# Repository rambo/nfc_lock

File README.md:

nfc_lock
========

(more) secure electric lock with DESFire EV1 NFC tags

## libnfc and libfreefare

    sudo apt-add-repository ppa:christopher-hoskin/ppa
    sudo apt-get update
    sudo apt-get install libnfc5 libnfc-bin libnfc-pn53x-examples libnfc-examples
    sudo apt-get install libfreefare0 libfreefare-bin
    sudo apt-get install python-zmq python-yaml python-tornado

`python-yaml` and `python-tornado` can be installed to virtualenv (esp tornado might be better to install via pip even if not to virtualenv the deb pulls unneccessary dependencies), zmq will be painful to install via pip, use the system package.

### For compiling

For the C programs.

    sudo apt-get install libfreefare-dev libnfc-dev libssl-dev pkg-config libzmq-dev

### RasPi

All libraries should be part of normal releases now.

## Terms

  - Card (PICC in NXP terms): The DESFire EV1 chip+antenna in a package (fob, card, sticker...)
  - Pre-Personalization step: Where card default master key is changed and applications are defined.
  - Application: collection of files on the card, application can have multiple keys for various purposes
  - Provisioning (or personalization) step: Where a personalized card is issued to a card holder and the card (plus backing datababase) is updated with relevant info
  - Diversified key: Key that has been derived from a master key via the method described in NXP AN19022

## SQLite for keys

Create a test file `sqlite3 keys.db`:

    CREATE TABLE valid_tokens (value TEXT UNIQUE, type INTEGER, acl INTEGER, external_ids TEXT);
    CREATE TABLE revoked_tokens (value TEXT UNIQUE, type INTEGER);

Prepare some tags and insert their (real) UIDs to the grants and revokes

    INSERT INTO revoked_tokens VALUES ("04453069b21e80");
    INSERT INTO valid_tokens VALUES ("04212f69b21e80", 0, 1);

In reality you will generate this file based on your person registry (keep track of validity times etc there, then regenerate the keydb for the door).

## Hacking

Remember to valgrind your C programs (`valgrind -v --leak-check=yes  myprog args`) at the same time as you do general functionality testing.

### RasPi

It seems Valgrind does not (and will not) support some instructions we use to talk with the NFC chips, see (this stackoverflow)[valgrindworkaround] for a workaround.

[valgrindworkaround]: http://stackoverflow.com/questions/20066215/valgrind-unrecognizes-memcmp-instruction-in-raspberry-pi#comment-29892760

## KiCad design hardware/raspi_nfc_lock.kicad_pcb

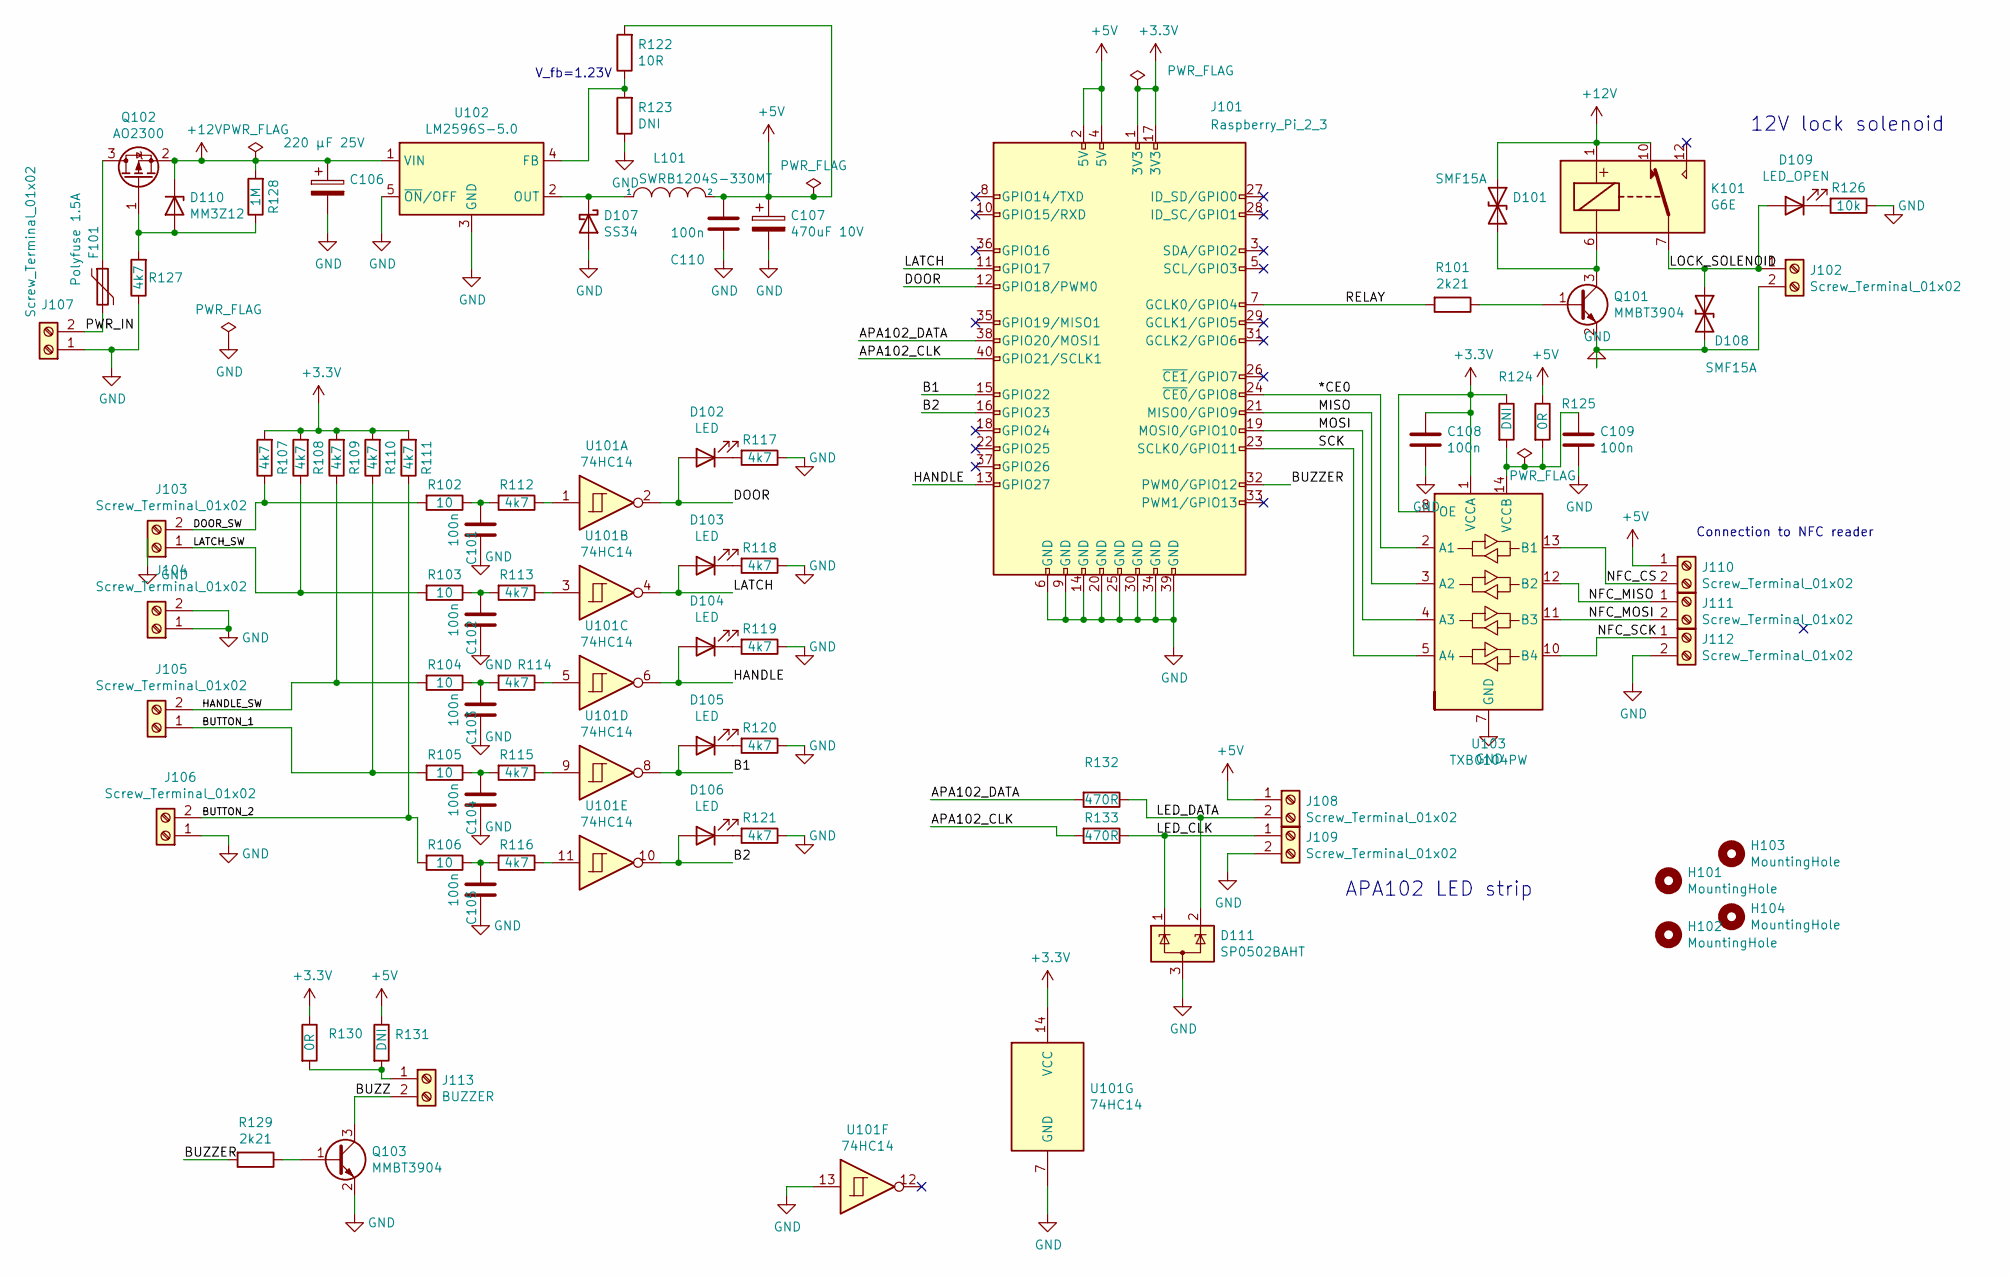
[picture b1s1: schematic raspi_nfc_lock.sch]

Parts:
C101, C102, C103, C104, C105, C108, C109: 100n; C_0603
C106: 220 μF 25V; CP_Elec_8x10
C107: 470uF 10V; CP_Elec_8x10.5
C110: 100n; C_1206
D101, D108: SMF15A; D_SOD-123
D102, D103, D104, D105, D106: LED; D_0603_1608Metric
D107: SS34; D_SMA
D109: LED_OPEN; D_0603_1608Metric
D110: MM3Z12; D_SOD-323
D111: SP0502BAHT; SOT-23
F101: Polyfuse 1.5A; Fuse_SMD2920
H101, H102, H103, H104: MountingHole; MountingHole_3.2mm_M3
J101: Raspberry_Pi_2_3; Pin_Header_Straight_2x20_Pitch2.54mm
J102, J103, J104, J105, J106, J107, J108, J109, J110, J111, J112: Screw_Terminal_01x02; TerminalBlock_Phoenix_MPT-0,5-2-2.54_1x02_P2.54mm_Horizontal
J113: BUZZER; TerminalBlock_Phoenix_MPT-0,5-2-2.54_1x02_P2.54mm_Horizontal
K101: G6E; Relay_SPDT_Omron_G6E
L101: SWRB1204S-330MT; L_12x12mm_H6mm
Q101, Q103: MMBT3904; SOT-23
Q102: AO2300; SOT-23
R101, R129: 2k21; R_0603
R102, R103, R104, R105, R106: 10; R_0603
R107, R108, R109, R110, R111, R112, R113, R114, R115, R116, R117, R118, R119, R120, R121, R127: 4k7; R_0603
R122: 10R; R_0603
R123, R124, R131: DNI; R_0603
R125, R130: 0R; R_0603
R126: 10k; R_0603
R128: 1M; R_0603
R132, R133: 470R; R_0603
U101: 74HC14; SOIC-14_3.9x8.7mm_P1.27mm
U102: LM2596S-5.0; TO-263-5_TabPin3
U103: TXB0104PW; TSSOP-14_4.4x5mm_P0.65mm

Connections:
+3V3: C108.1, J101.1 (3V3), J101.17 (3V3), R107.2, R108.2, R109.2, R110.2, R111.2, R124.1, R130.1, U101.14 (VCC), U103.1 (VCCA), U103.8 (OE)
+5V: C107.1, C110.2, J101.2 (5V), J101.4 (5V), J108.1, J110.1, L101.2, R122.2, R125.1, R131.1
+12V: C106.1, D101.1 (A1), D110.1 (K), K101.1, K101.10, Q102.2 (S), R128.2, U102.1 (VIN)
/*CE0: J101.24 (~CE0~/GPIO8), U103.2 (A1)
/APA102_CLK: J101.40 (GPIO21/SCLK1), R133.2
/APA102_DATA: J101.38 (GPIO20/MOSI1), R132.2
/B1: D105.2 (A), J101.15 (GPIO22), U101.8
/B2: D106.2 (A), J101.16 (GPIO23), U101.10
/BUTTON_1: J105.1, R105.2, R110.1
/BUTTON_2: J106.2, R106.2, R111.1
/BUZZ: J113.2, Q103.3 (C)
/BUZZER: J101.32 (PWM0/GPIO12), R129.2
/DOOR: D102.2 (A), J101.12 (GPIO18/PWM0), U101.2
/DOOR_SW: J103.2, R102.2, R107.1
/HANDLE: D104.2 (A), J101.13 (GPIO27), U101.6
/HANDLE_SW: J105.2, R104.2, R109.1
/LATCH: D103.2 (A), J101.11 (GPIO17), U101.4
/LATCH_SW: J103.1, R103.2, R108.1
/LED_CLK: D111.1 (K), J109.1, R133.1
/LED_DATA: D111.2 (K), J108.2, R132.1
/LOCK_SOLENOID: D108.1 (A1), D109.2 (A), J102.1, K101.7
/MISO: J101.21 (MISO0/GPIO9), U103.3 (A2)
/MOSI: J101.19 (MOSI0/GPIO10), U103.4 (A3)
/NFC_CS: J110.2, U103.13 (B1)
/NFC_MISO: J111.1, U103.12 (B2)
/NFC_MOSI: J111.2, U103.11 (B3)
/NFC_SCK: J112.1, U103.10 (B4)
/PWR_IN: F101.2, J107.2
/RELAY: J101.7 (GCLK0/GPIO4), R101.2
/SCK: J101.23 (SCLK0/GPIO11), U103.5 (A4)
GND: C101.1, C102.1, C103.1, C104.1, C105.1, C106.2, C107.2, C108.2, C109.2, C110.1, D107.2 (A), D108.2 (A2), D111.3 (A), J101.6 (GND), J101.9 (GND), J101.14 (GND), J101.20 (GND), J101.25 (GND), J101.30 (GND), J101.34 (GND), J101.39 (GND), J102.2, J104.1, J104.2, J106.1, J107.1, J109.2, J112.2, Q101.2 (E), Q103.2 (E), R117.1, R118.1, R119.1, R120.1, R121.1, R123.1, R126.1, R127.1, U101.7 (GND), U101.13, U102.3 (GND), U102.5 (~ON~/OFF), U103.7 (GND)
unnamed: C101.2, R102.1, R112.2
unnamed: C102.2, R103.1, R113.2
unnamed: C103.2, R104.1, R114.2
unnamed: C104.2, R105.1, R115.2
unnamed: C105.2, R106.1, R116.2
unnamed: C109.1, R124.2, R125.2, U103.14 (VCCB)
unnamed: D101.2 (A2), K101.6, Q101.3 (C)
unnamed: D102.1 (K), R117.2
unnamed: D103.1 (K), R118.2
unnamed: D104.1 (K), R119.2
unnamed: D105.1 (K), R120.2
unnamed: D106.1 (K), R121.2
unnamed: D107.1 (K), L101.1, U102.2 (OUT)
unnamed: D109.1 (K), R126.2
unnamed: D110.2 (A), Q102.1 (G), R127.2, R128.1
unnamed: F101.1, Q102.3 (D)
unnamed: J113.1, R130.2, R131.2
unnamed: Q101.1 (B), R101.1
unnamed: Q103.1 (B), R129.1
unnamed: R112.1, U101.1
unnamed: R113.1, U101.3
unnamed: R114.1, U101.5
unnamed: R115.1, U101.9
unnamed: R116.1, U101.11
unnamed: R122.1, R123.2, U102.4 (FB)

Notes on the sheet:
APA102 LED strip
12V lock solenoid
V_fb=1.23V
Connection to NFC reader

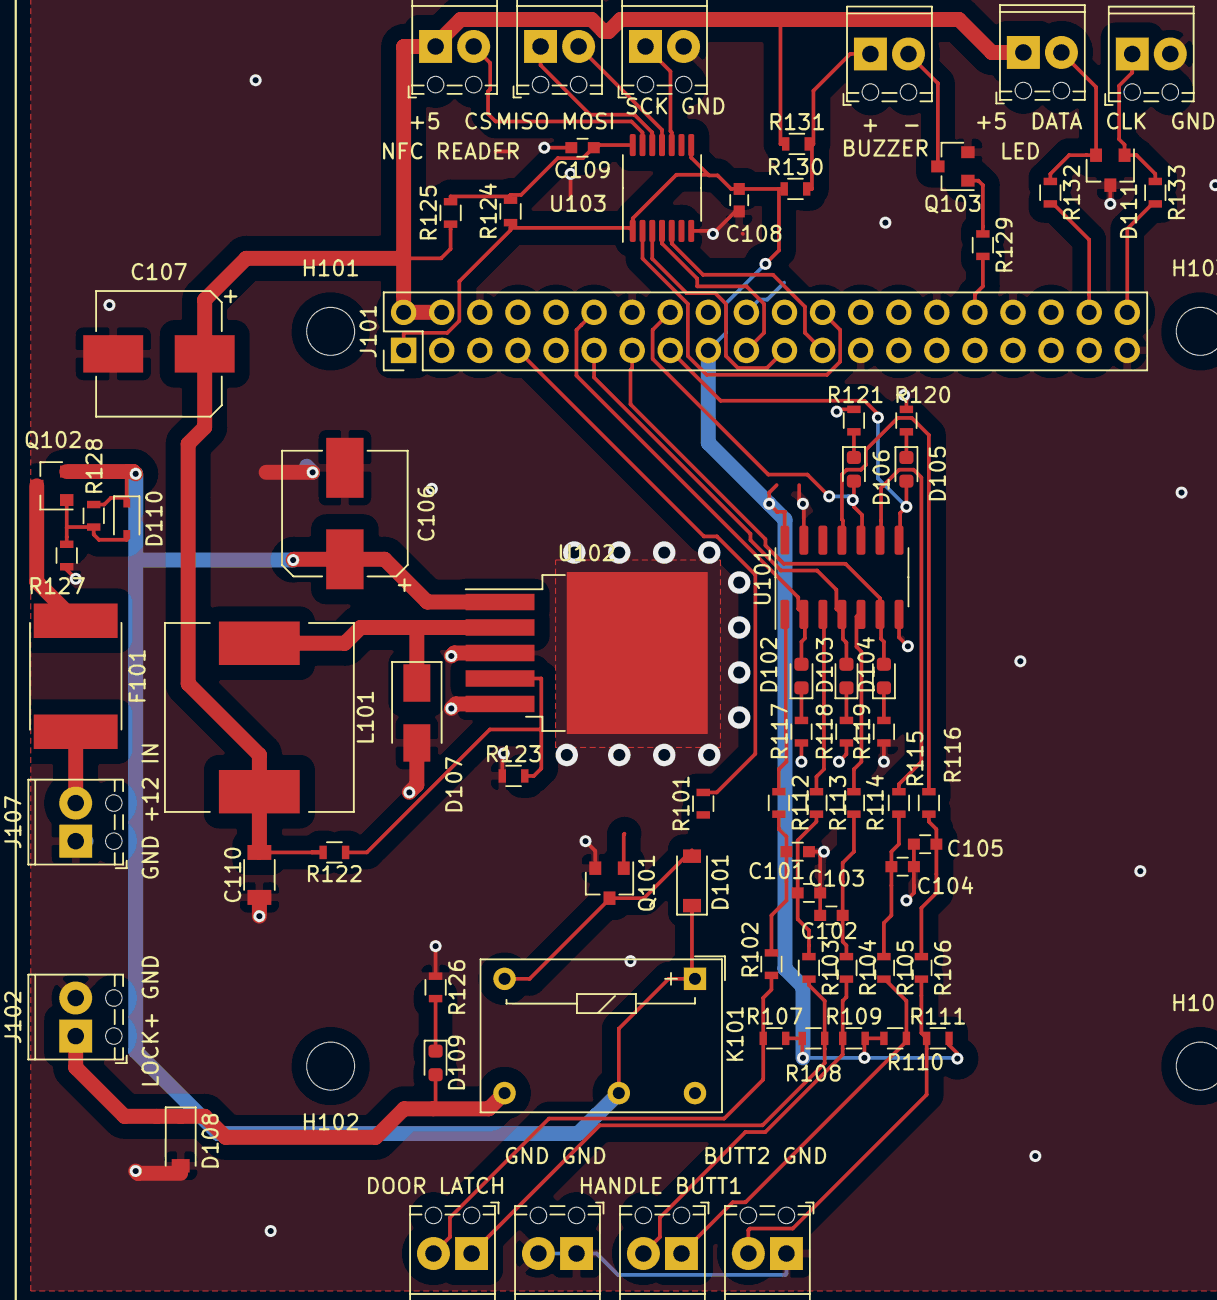
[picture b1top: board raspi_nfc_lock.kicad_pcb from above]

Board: 2 copper layers, 80 parts (0 on the bottom side), 56 nets.

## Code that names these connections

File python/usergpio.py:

import os
import time
import struct

class gpiopin(object):
    _filename = None
    _fh = None
    _pin = None
    _inverted = False


    def __init__(self, pinnumber, dir="in", inverted=False):
        iodir = "/sys/class/gpio"
        self._filename = f"{iodir}/gpio{pinnumber}"
        #Export pin if not there
        if not os.path.isfile(f"{iodir}/gpio{pinnumber}/direction"):
            with open(f"{iodir}/export", "w") as f:
                f.write("%d\n" % pinnumber)
        with open(f"{iodir}/gpio{pinnumber}/direction", "w") as dirfile:
            dirfile.write(f"{dir}\n")
        if dir == "in":
            self._fh = open(f"{iodir}/gpio{pinnumber}/value", "rb", 0)
        else:
            self._fh = open(f"{iodir}/gpio{pinnumber}/value", "wb", 0)
        self._pin = pinnumber
        self._inverted = inverted

    def __del__(self):
        if self._fh:
            self._fh.close()
        
    def set(self, state):
        state = state^self._inverted
        if state:
            self._fh.write(b'1')
        else:
            self._fh.write(b'0')

    def get(self):
        self._fh.seek(0)
        if int(self._fh.read())^self._inverted:
            return 0
        return 1

RGBTABLE = {
    'R': [200, 0, 0],
    'r': [40, 0, 0],
    'G': [0, 255, 0],
    'g': [0, 60, 0],
    'B': [0, 0, 255],
    'b': [0, 0, 60],
    'y': [60, 40, 0],
    'Y': [255, 200, 0],
    'M': [200, 0, 255],
    'm': [40, 0, 60],
    'W': [255, 255, 255],
    'w': [60, 60, 60],
    ' ': [0,0,0],
    '.': [0,0,0]
}

class ledstring(object):
    _clkpin = None
    _datapin = None
    _nleds=1

    def __init__(self, data_pin=20, clk_pin=21, n=1):
        self._clk = gpiopin(clk_pin, "out")
        self._data = gpiopin(data_pin, "out")
        self._nleds = n

    def _out(self, data):
        for outbyte in data:
            for bit in range(7,-1,-1):
                self._clk.set(0)
                d=((outbyte&(1<<bit))>>bit)
                self._data.set(d)
                self._clk.set(1)
        self._clk.set(0)

    def _send_rgb(self,r,g,b):
        current = 16 #out of 31
        #Send global current + 3 PWM values with 0b111 starting bits
        self._out(struct.pack("BBBB", 224+current, b, g, r))

    def _start_of_frame(self):
        self._out(b"\x00\x00\x00\x00")

    def _end_of_frame(self):
        self._out(b"\xff\xff\xff\xff")
        
    def set_all_rgb(self, r,g,b):
        self._start_of_frame()
        for ledno in range(self._nleds):
            self._send_rgb(r,g,b)
        self._end_of_frame()
        self._start_of_frame()
        self._start_of_frame()

    #Sets LEDs with string like "RRRGGGBBB"
    def setstr(self, colors):
        self._start_of_frame()
        for c in colors:
            self._send_rgb(RGBTABLE[c][0], RGBTABLE[c][1], RGBTABLE[c][2])
        self._end_of_frame()
        #self._start_of_frame()
        #self._start_of_frame()

if __name__ == "__main__":
    relay = gpiopin(4, dir="out")
    buzzer = gpiopin(12, dir="out")
    led_clk = gpiopin(20, dir="out")
    led_data = gpiopin(21, dir="out")
    latch = gpiopin(17, dir="in")
    door = gpiopin(18, dir="in")
    b1 = gpiopin(22, dir="in")
    b2 = gpiopin(23, dir="in")
    handle = gpiopin(27, dir="in")
    
    for i in range(100):
        relay.set(0)
        #buzzer.set(0)
        time.sleep(0.5)
        relay.set(1)
        #buzzer.set(1)
        time.sleep(0.5)

        print(f"latch={latch.get()} door={door.get()} handle={handle.get()} b1={b1.get()} b2={b2.get()}")
        

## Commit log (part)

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2014-10-25 ignore OSX extra files
2014-10-25 some diagrams, originally drawn for http://skeemipesa.ee/tehnohack/en/
2014-10-25 debs built on raspbian wheezy (from jessie source packages)
2014-10-25 Go freefare package dependencies
2014-10-25 open the first libnfc configure device and print info
2014-10-25 remove the hello-world
2014-10-25 YAML parsing and hex-decoding test
2014-10-25 trying to figure out how to handle key diversification
2014-10-25 set the block limits correcty(?)
2014-10-25 add the 0x01 DIV constant
2014-10-25 implement using the test values from the AN
2014-10-25 fix key diversification for card sourced version
2014-10-25 simple poller
2014-10-25 run a heartbeat while polling for tags
2014-10-25 check the tag
2014-10-25 GPIO (untested)
2014-10-26 the constants are not up-to-date for B+
2014-10-26 cast correctly
2014-10-26 handle the relay too, refactor the teardown on interrupt
2014-10-26 rename the interrupt channel
2014-10-26 Added test program for desfire
2014-10-26 check ACL on raspi too
2014-10-26 use the default device
2014-10-26 sudo, hide the go install dir
2014-11-06 Started writing provisioning library by adding README.
2014-11-06 Added list of items to be commited.
2014-11-08 make a module out of this
2014-11-08 rename the function
2014-11-08 use the diversification library
2014-11-08 rethinking the applications and keys
2014-11-08 note about values being hex
2014-11-08 the GPIO config is node related and this way we still have 3 instead of 4 config files
2014-11-08 the canonical GPIO test cocode, LED blinker
2014-11-08 initially we just change the default key
2014-11-08 return nil as the value if there is an error
2014-11-09 UNTESTED: setting application keys
2014-11-09 some code to revert card back to clean state when we have fscked up
2014-11-09 tried to change order of key changes but still getting "unknown error", which most likely is actually authentication error (due to old libfreefare not setting errno correctly on authentication erorrs
2014-11-09 the first step is pre-personalization
2014-11-09 reminder to use backupfile for the ACL data too
2014-11-09 null AES key auth before changing application key 0 (aka provisioning key) worked, but getting problems when trying to change the other keys
2014-11-09 helper to calculate the settings flag (hopefully correctly)
2014-11-09 clean up old commented out code, update comments elsewhere
2014-11-09 make a module for the helpers (and rename them to start with capital letter so they are exported)
2014-11-09 make the YAML loading song&dance a helper
2014-11-09 read the ACL data back to uint64 so we can use boolean math to check for flags
2014-11-09 use the configured file ids here too, for some reason the second data file is not read fully...
2014-11-09 renamed the program
2014-11-09 for some reason the commit gives error, though AFAIUnderstand it must be done for backed up data files... changes are saved though
2014-11-09 fix tabs
2014-11-09 make it clear which data needs to be moved to personnel registry too
2014-11-09 found a bug while refactoring, the binary unpacking does not work as expected here
2014-11-09 started writing the actual relay controlling program, based on the test_gpio.go
2014-11-09 check for revoked keys
2014-11-09 explicit calld to disconnect since reconnecting to an already active tag will fail
2014-11-10 display the errors for connect too and retry
2014-11-11 try to optimize the memory use a bit, did not help with the weird malloc errors though
2014-11-11 heavy-handed refactoring
2014-11-11 remember to make those indices unique, also some notes about integer types
2014-11-11 it seems I was thinking of some other type casting issue
2014-11-11 refactored the card checking into a function
2014-11-11 fix logic error
2014-11-11 actually fix the logic error
2014-11-12 use different sqlite library
2014-11-12 also old code using old sqlite library and for prototyping anyway
2014-11-12 the channel version of course must be called as goroutine...
2014-11-12 senders close, receivers check for closed
2014-11-12 remove some (probably) unneccessary stuff
2014-11-14 trying to debug a segfault
2014-11-14 do not panic if gettags fauils
2014-11-14 disable GPIO since it fscks up gdb (due to epoll returning error instead of retrying on EINTR
2014-11-14 yes, getting desperate. memory is still corrupted somewhere
2014-11-14 skip profiling
2014-11-14 do this many times
2014-11-14 read in a loop to trigger memory error
2014-11-14 slightly more robust version, still crashes though
2014-11-14 do not slice
2014-11-15 check if passing the tag as pointer would cause a problem, not yet...
2014-11-15 just connecting and disconnecting does not seem to be enough to mess the heap
2014-11-15 this does not yet crash
2014-11-15 still no crash
2014-11-15 then again this does NOT crash
2014-11-15 switching to uint32 for ACL seems to work fine... go figure...
2014-11-15 after a couple of succesfull reads I now keep getting "unknown error" when re-authenticatingwith the ACL-read key (either key diversification gets fscked or something goes wrong in libfreefare
2014-11-15 this does not help with the "unknown error"
2014-11-15 it seems these two approaches return different result... anyway we lose the first byte at some poitn for reasons unknown...
2014-11-15 this seems reliable though
2014-11-15 let it run long enough and fatal error: markallocated: bad pointer
2014-11-15 be less noisy
2014-11-15 link to correct blog post
2014-11-15 ACL is now uint32 since with uint64 hings were crahsing left and right on x86 as well (where testing and debugging is easier)
2014-11-15 trying to compile these outside of libfreefare distribution
2014-11-15 I guess the first way is simpler
2014-11-15 test that the CMAC example compiles
2014-11-15 missed this one...
2014-11-15 add debugs
2014-11-15 need to pass the size correctly to the comparison function too
2014-11-15 make it possible to specify from cli how many times to run
2014-11-15 example headers for configuring keys etc
2014-11-15 opening the device works if I give the connstring from cli, the default "" does not...
2014-11-15 poll for tags, libfreefare seems to leak memory :(
    ==7894== HEAP SUMMARY:
    ==7894== in use at exit: 475 bytes in 41 blocks
    ==7894== total heap usage: 641 allocs, 600 frees, 64,749 bytes
    allocated
    ==7894==
    ==7894== Searching for pointers to 41 not-freed blocks
2014-11-15 ah, the other leak was my fault too...
    ==7932== HEAP SUMMARY:
    ==7932== in use at exit: 0 bytes in 0 blocks
    ==7932== total heap usage: 629 allocs, 629 frees, 61,243 bytes
    allocated
    ==7932==
    ==7932== All heap blocks were freed -- no leaks are possible
2014-11-15 mark the memory leak
2014-11-15 pass the tag to a handler function, so far so good
2014-11-15 print out what we actually parsed as the aid bytes
2014-11-15 selecting application works
2014-11-15 static key auth works
2014-11-16 pass the UID as string to key diversification because that is the way we get it from libfreefare
2014-11-16 prefix the helper too
2014-11-16 print the intermediate key bytes for debugging
2014-11-16 re-auth with ACL read key
2014-11-16 reading membership-id file
2014-11-16 tried to do something about the leak triggered by nfc_list_devices
2014-11-16 note about the timeout
2014-11-16 timeouts with pthreads but seems to leak
    ==10602== HEAP SUMMARY:
    ==10602== in use at exit: 1,632 bytes in 6 blocks
    ==10602== total heap usage: 736 allocs, 730 frees, 79,777 bytes
    allocated
    ==10602==
    ==10602== Searching for pointers to 6 not-freed blocks
2014-11-16 use phtread exit on the example too, but it too (possibly) leaks memory...
    do_or_timeout: calculation timed out
    --10711-- REDIR: 0x50d8870 (free) redirected to 0x4c2bd80 (free)
    ==10711==
    ==10711== HEAP SUMMARY:
    ==10711== in use at exit: 272 bytes in 1 blocks
    ==10711== total heap usage: 1 allocs, 0 frees, 272 bytes allocated
2014-11-16 cleaner way (also works when the infite loop is commented out)
2014-11-16 no leaks, yay!
2014-11-16 remove dead code, improve comments, add sanity-checks and defensive programming
2014-11-17 Added targets for different binaries.
2014-11-17 Fixed targets `all` and `clean`.
2014-11-17 Revert "Added list of items to be commited."
    This reverts commit 17f50deb2c7b290dcb1d74f95d18eb6c8d07dff4.
2014-11-17 Revert "Started writing provisioning library by adding README."
    This reverts commit 509e30bafb4f2d7743b81e3ccf9e4f74d4b1a0f4.
2014-11-24 loop and use correct receive method
2014-11-24 specify the uid on cli
2014-11-24 see if we can do event-based REQ/REP like this
2014-11-24 stub for serving key info over ZMQ
2014-11-24 still stub, config loading implemented
2014-11-24 the ioloop
2014-11-24 moar deps
2014-11-24 musings about logging the seen cards
2014-11-24 stub for accessing the python ZQM-REP server
2014-11-24 this juggling of libs flags did nothing
2014-11-24 remove the incorrect example code I copied for reference, this now works for receiving N part messages
2014-11-25 copy the read test as base for the actual gatekeeper
2014-11-25 add gatekeeper to Makefile
2014-11-25 fix comments
2014-11-25 output messages from ZMQ only in case of trouble
2014-11-28 better context name
2014-11-28 bind to pubsub socket, refactor string sending to a helper
2014-11-28 QnD test code for publish and subscribe
2014-11-28 all topics sub example
2014-11-28 use the result as topic, close the socket we failed to open before terminating the context or zmq hangs...
2014-12-01 trivial helper to handle gpio via sysfs
2014-12-01 copied configs for the old watcher, QnD ZMQ "port" (does not yet actually act upon cards)
2014-12-01 bypass couchdb errors when logging
2014-12-01 add FAKE mode for testing on VMs etc
2014-12-01 handle the results coming over ZMQ
2014-12-03 small breakout for three status leds
2014-12-04 on raspbian we must specify -lrt
2014-12-04 note about a problem when perosnalizing
2014-12-08 QnD upstart scripts based on old ones from elsewhere
2014-12-08 script to make a tarball you can uncompress on your target node so it does not have to contain the build dependencies
2014-12-08 leave the directory before removing it
2014-12-08 be quiet
2014-12-09 start pre-personalization code based on the read_personalized code
2014-12-09 make a separate program for formatting the card (de-personalize)
2014-12-09 keep the nullkey as global
2014-12-09 print the errors
2014-12-09 this seems to make no difference either way
2014-12-09 still getting LENGTH_ERROR when trying to change the Application master key
2014-12-09 at least I get different error but I cannot figure out when I should use the set_default_key and when change_key
2014-12-09 this function specifies the crypto anyway
2014-12-10 the "member-id" (to be renamed) file will contain a pseudorandom uint32 that is unique and persistent for a person in our system
2014-12-10 convert to use the helpers
2014-12-10 QnD personalization tool still needs work
2014-12-11 reading the value from the card works fine but for some reason the stack protector does not like us when we try to assign the value
2014-12-11 no need to init these
2014-12-11 do not leak memory
2014-12-11 enable random-id, do not leak
2014-12-11 updated the table telling where various keys are needed
2014-12-11 updated the concept, we have only one application
2014-12-14 sleep less if the personalization failed
2014-12-14 explicitly enable the stack protector
2014-12-14 note about valgrind on raspi
2015-01-15 logging helpers
2015-01-15 added important reminder
2015-02-18 it seems that for UPiS NO is the new NC, and we have to use external relay...
2015-03-24 list log.c only once
2015-03-24 use the log helpers for messages
2015-03-24 ignore the log_test binary
2017-03-18 Ignore IDE files
2017-03-18 Update README for new format db
2020-05-20 Updated ZMQ calls to current version
2020-05-24 Updated zqm calls
2020-05-24 Python3 string/bytes update
2020-05-24 Added heartbeat and installation items
2020-05-28 Fixed key db origin path
2020-05-28 Moved ZMQ to localhost instead of 0.0.0.0
2020-07-29 Added missing systemd service files
